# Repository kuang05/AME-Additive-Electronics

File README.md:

# AME · 增材电子一体化软件

> 从三维结构与 PCB 设计，到可打印的双材料 G-code —— 并把"这块板到底打不打得出来"量化成 0–100 分。

华为 ICT 大赛创新赛 · 赛题一（基于华为云产品打造 AI 创新应用）参赛作品。

---

## 这个软件解决什么问题

传统 PCB 打样依赖蚀刻、曝光、电镀，周期长、门槛高；普通 3D 打印机只能打塑料，不懂电气连接。

本软件把"电气设计"和"增材制造"接起来，回答一个两边都不回答的问题：

> **这块板，按这台机器、这套材料，到底打不打得出来？**

不做原理图编辑、不做三维建模、不做多机调度。只做"从已有设计到可打印路径"这一层，

并把可打性量化成规则与分数。

---

## 核心能力（四域 + 智能体）

| 域 | 能力 | 关键实现 |

|---|---|---|

| **结构** | STEP 导入（AP203/214/242，mm/inch，含装配体展平）、几何诊断、面分析、布尔建议预览、剖切测量 | 自研 B-Rep 平面/柱面/圆锥/球面/环面解析，18 类诊断码，3 份真实 CAD 文件实测 |

| **走线** | 板文件导入（KiCad/网表）、器件放置、手动布线、A* 自动布线、跳线、连通性检查 | 8 邻域栅格寻路 + 转弯惩罚 + 禁布区避让 |

| **可打性** | 七条工艺规则、0–100 评分、问题定位、中文原因与建议、热力图 | R1 线宽 / R2 间距 / R3 坡度 / R4 可达性 / R5 遮挡 / R6 温度场 / R7 介电流道 |

| **切片** | 三层双材料道次编排、坝-槽-坑几何、G-code 导出（确定性可复现） | 7 道次 / 总厚 0.44 mm；同一设计两次导出哈希一致 |

| **打印** | 虚拟打印、暂停/恢复、故障注入、缺陷归因、断电续打 | 缺陷归因到 设计/工艺/设备 三类 |

| **智能体** | 设计 Agent（检查→改→复检）、审查、裁决、计划重放 | 60 → 94 分；重放时设计摘要与 G-code 哈希双一致 |

**AI 有两条路径，定位不同**：

| 路径 | 定位 | 说明 |

|---|---|---|

| 华为云 **MaaS** 大模型（`ai/maas.py`） | **主线** | 赛题要求"调用大模型"。把规则违规翻译成可执行建议、做候选语义重排。OpenAI 兼容接口，默认 DeepSeek-V3-32K |

| 本地 26 维线性排序器（`ai/local.py`） | **离线降级** | 未配置密钥/断网时兜底。**这不是神经网络**——是解一次线性方程得到的系数，详见 [AI证据链.md](AI证据链.md) §0 |

降级链：MaaS → 本地线性 → 规则先验，任一层失败都不影响主流程。

---

## 两种交付形态，同一套算法内核

```

              ┌───────────────────────────────┐

              │  四域算法内核（约 6500 行）    │

              │  geometry / mrc / slicing /   │

              │  circuit / printing / ai      │

              │  纯函数，无数据库、无界面依赖  │

              └────────────┬──────────────────┘

                           │

                ┌──────────┴──────────┐

                │  ledger 命令总线     │

                │  （唯一写入口）      │

                └──────────┬──────────┘

                 ┌─────────┴─────────┐

           ┌─────┴─────┐       ┌─────┴──────┐

           │ 桌面版     │       │ 云上 Demo  │

           │ Tkinter   │       │ FastAPI    │

           │ AME.exe   │       │ 浏览器画布  │

           └─────┬─────┘       └─────┬──────┘

           ┌─────┴─────┐       ┌─────┴──────┐

           │  SQLite   │       │ RDS PG +   │

           │ 本地文件   │       │ Redis      │

           └───────────┘       └────────────┘

```

**有测试断言"同一设计在两端算出的分数完全相同"**——证明上云是换壳而非另写一套。

云上画布除了四域闭环，还做了六项查看/编辑交互（`tests/test_web_features.py` 24 项锁定）。

其中五项桌面版早有对应入口，**版本历史面板是这边第一次做成可浏览的界面**

（桌面版只在顶栏显示「版本 N」，PRJ-004 的数据一直在账本里、没有列表视图）：

| 交互 | 后端 | 说明 |

|---|---|---|

| 逐层播放 | `GET /api/projects/{pid}/layer/{index}` | 滑块 + 上/下一道次 + 起停点标记；路径取自库中那份切片，不重算 |

| 问题定位 | `GET /api/projects/{pid}/state` | 点问题列表自动高亮对应走线/焊盘 |

| 热力图 | `GET /api/projects/{pid}/heatmap` | 开关切换叠加，按对象累计扣分 |

| 规则阈值编辑 | `GET/POST /api/projects/{pid}/rules[/{code}]` | 七条规则逐个改阈值/启停；改阈值使规则版本 +1，保存即重评分（仅切启停不改版本） |

| 版本历史 | `GET /api/projects/{pid}/versions` | 每版序号、原因、分数前后与变更项 |

| 剖切 Z 阈值 | `GET /api/projects/{pid}/state` | 三维视图只画 Z ≤ 阈值的面，判据与桌面版一致 |

`state` 接口的 `faces` 带 `loop` / `normal` / `centroid` 顶点数据（超过 4000 个面时只下发前 4000 个，

并在 `faces_note` 说明被截断）。

---

## 快速开始

### 方式一：桌面版（离线，零依赖）

```bash

pip install shapely numpy pillow

python -m ame                    # 启动界面

python -m ame --selftest         # 11 步无界面自检

```

或用打包版：解压 `dist/AME/`，双击 `AME.exe`。

首次启动 → 工程 → 打开示例工程（一键看到完整链路）。

### 方式二：云上 Demo（浏览器）

```bash

pip install -r requirements-cloud.txt

python -m uvicorn ame.web.app:app --port 8000

# 打开 http://127.0.0.1:8000

```

或用 Docker：

```bash

docker compose up --build        # 含 PostgreSQL + Redis

```

### 方式三：接华为云 RDS + Redis

```bash

export AME_PG_DSN="postgresql://user:pass@<rds-host>:5432/ame"

export AME_REDIS_URL="redis://<redis-host>:6379/0"

python -m uvicorn ame.web.app:app --host 0.0.0.0 --port 8000

curl http://127.0.0.1:8000/api/health   # storage 应为 postgresql

```

详见 [云上部署与比赛材料.md](云上部署与比赛材料.md)。

---

## 复现验证（组委会按材料核对时用这个）

```bash

# 1. 全量测试（不含性能基准，约 8 分钟，离线）

python -m pytest -q -m "not perf"

# 2. 质量门禁（10 项客观指标）

python check_quality.py --full

# 3. 桌面版自检（11 步，无需显示环境）

python -m ame --selftest

# 4. 云端接口自检

python -m uvicorn ame.web.app:app --port 8000 &

curl -X POST http://127.0.0.1:8000/api/projects/sample

```

**预期结果**：886 项测试通过、2 项跳过（本机无 PostgreSQL，`psycopg` 未安装）；

门禁 9/10（`ame/geometry/stepio.py` 1384 行超出 1200 行阈值，其余 9 项通过）；

自检 11 步全过；示例工程 60 分 / 12 条问题；切片 7 道次 / 0.44 mm。

---

## 项目结构

```

ame/

├── ai/            收益排序（features / local / cloud / service / train）

├── agent/         设计·审查·裁决 Agent 与计划重放

├── circuit/       connectivity(判定) + routing(寻路) + kicad(导入)

├── db/            store(读写) + pg_store(PG) + storage(协议) + migrations + cache

├── geometry/      vec3 → types → syntax → assembly → stepio（严格单向依赖）

├── ledger/        errors + commands(写) + workspace(状态) + services

├── mrc/           engine（7 条规则，每条一个函数）

├── printing/      virtual（虚拟打印机与缺陷注入）

├── slicing/       raster(路径) + slicer(道次) + gcode(导出)

├── ui/            theme + app + _shell + _canvas + domains/*（7 个域）

└── web/           app(FastAPI) + static/index.html（浏览器画布）

```

读代码建议顺序：`ledger/commands.py` 的模块 docstring（写入口不变量）

→ `workspace.mrc_state()`（数据如何组装）→ 各域实现。

---

## 工程数据

| 指标 | 数值 |

|---|---|

| 代码规模 | `ame` 15,849 行 / 59 个模块 |

| 测试 | 710 项通过 + 2 项跳过（22 个测试文件） |

| 静态检查 | `ruff check ame/` 零违规 |

| 业务层类型注解 | 返回 76.6% / 参数 68.8% |

| 最大模块 | 1384 行（`geometry/stepio.py`；重构前为 3502 行的 `ui/app.py`） |

| 真实 CAD 验证 | 3 份（PRO/ENGINEER、Open CASCADE、SolidWorks，共约 800 KB） |

---

## 已知边界（主动说明）

| 边界 | 说明 |

|---|---|

| STEP 曲面 | 平面/柱面/圆锥（含圆台）/球面/环面可解析（面积用解析公式，三角网格只用于 `loop` 渲染，不参与面积）；B 样条/NURBS 等自由曲面仍不支持，标 `G-SURFACE-UNSUPPORTED`，面积取"包围盒与三角扇的较小值"保守低估。环面与球冠侧别不可判定时标 `G-SURFACE-APPROX` |

| 布尔运算 | 只做预览不执行（需求 V1 范围） |

| 真机联调 | 仅虚拟打印机，串口/网络协议已预留 |

| 多层过孔 | 首版不支持双层过孔与连续曲面切片 |

| 云上多用户 | 当前单用户演示；多租户需换 Redis 会话 + 每请求校验 |

| MindSpore/昇腾 | **未使用，也不宣称**。赛题一要求的是华为云产品（CodeArts/RDS/Redis），这三项均已接入 |

| PostgreSQL 实测 | 代码与方言转换已完成；本机（Python 3.13）无 psycopg wheel，真实 PG 集成需在有 RDS 时执行 |

---

## 文档索引

| 文档 | 内容 |

|---|---|

| [云上部署与比赛材料.md](云上部署与比赛材料.md) | 赛题一对应关系、部署步骤、CodeArts 留证、评委问答准备 |

| [赛题一改造方案.md](赛题一改造方案.md) | 云原生化技术裁决与施工记录 |

| [验收报告.md](验收报告.md) | 验收结论、测试分布、逐项实测记录 |

| [AI证据链.md](AI证据链.md) | 先说明「这里的 AI 是什么」、拟合数据、LOSO 交叉验证、降级链测试 |

| [重构记录.md](重构记录.md) | 架构拆分（模块边界、搬运方法、未做的取舍） |

| [质量提升记录.md](质量提升记录.md) | 缺陷清单、覆盖率、静态检查整改 |

| [用户操作说明.md](用户操作说明.md) | 五分钟演示路径、概念速查、快捷键 |

| [增材电子一体化软件_需求规格说明书.md](增材电子一体化软件_需求规格说明书.md) | 需求基线（唯一验收依据） |

---

## 许可

本项目采用 **Apache License 2.0**，详见 [LICENSE](LICENSE)。

允许商业使用、修改、分发，需保留版权声明与许可文本。

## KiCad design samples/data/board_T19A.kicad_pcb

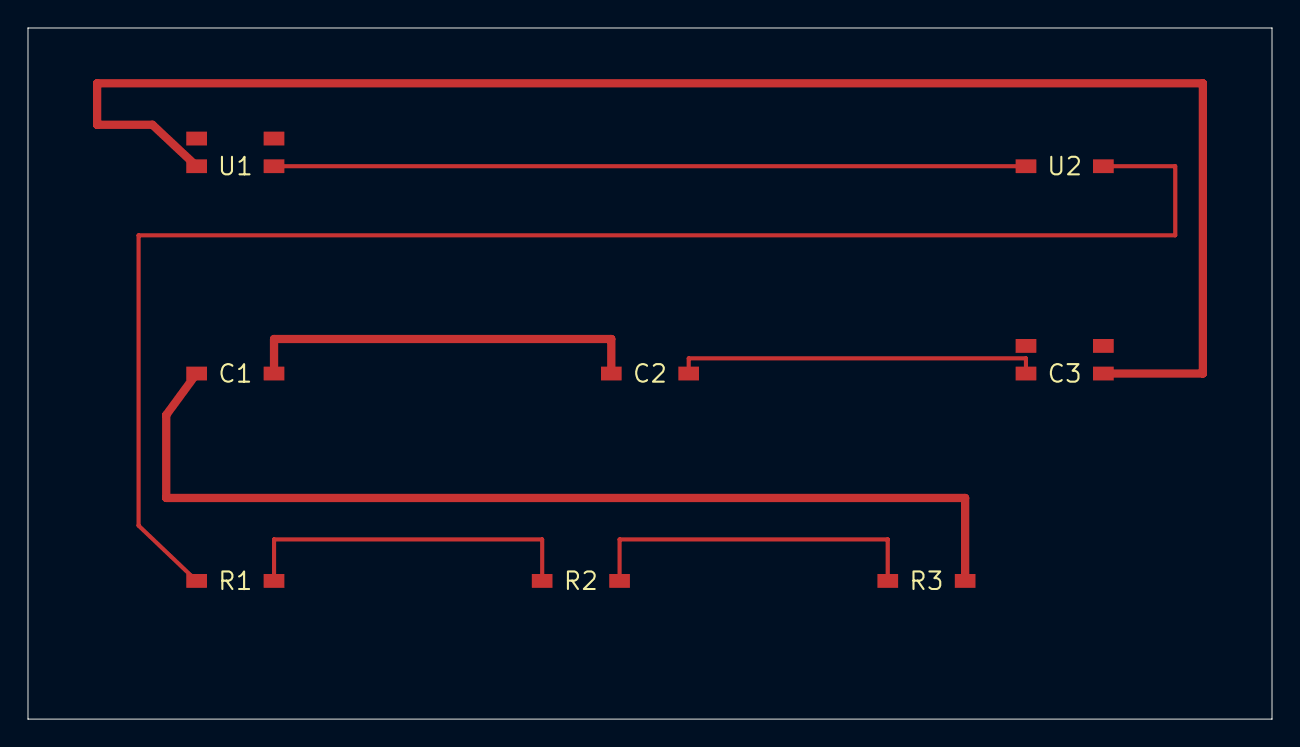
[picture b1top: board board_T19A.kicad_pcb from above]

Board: 0 copper layers, 90.0 x 50.0 mm, 8 parts (0 on the bottom side), 8 nets.

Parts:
C1, C2: R0603
C3: QFN8
R1, R2, R3: R0603
U1: QFN8
U2: R0603

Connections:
GND: C3.2, U1.1
N1: R1.1, U2.2
N2: R1.2, R2.1
N3: R2.2, R3.1
N4: C1.1, R3.2
N5: C1.2, C2.1
N6: C2.2, C3.1
VCC: U1.2, U2.1

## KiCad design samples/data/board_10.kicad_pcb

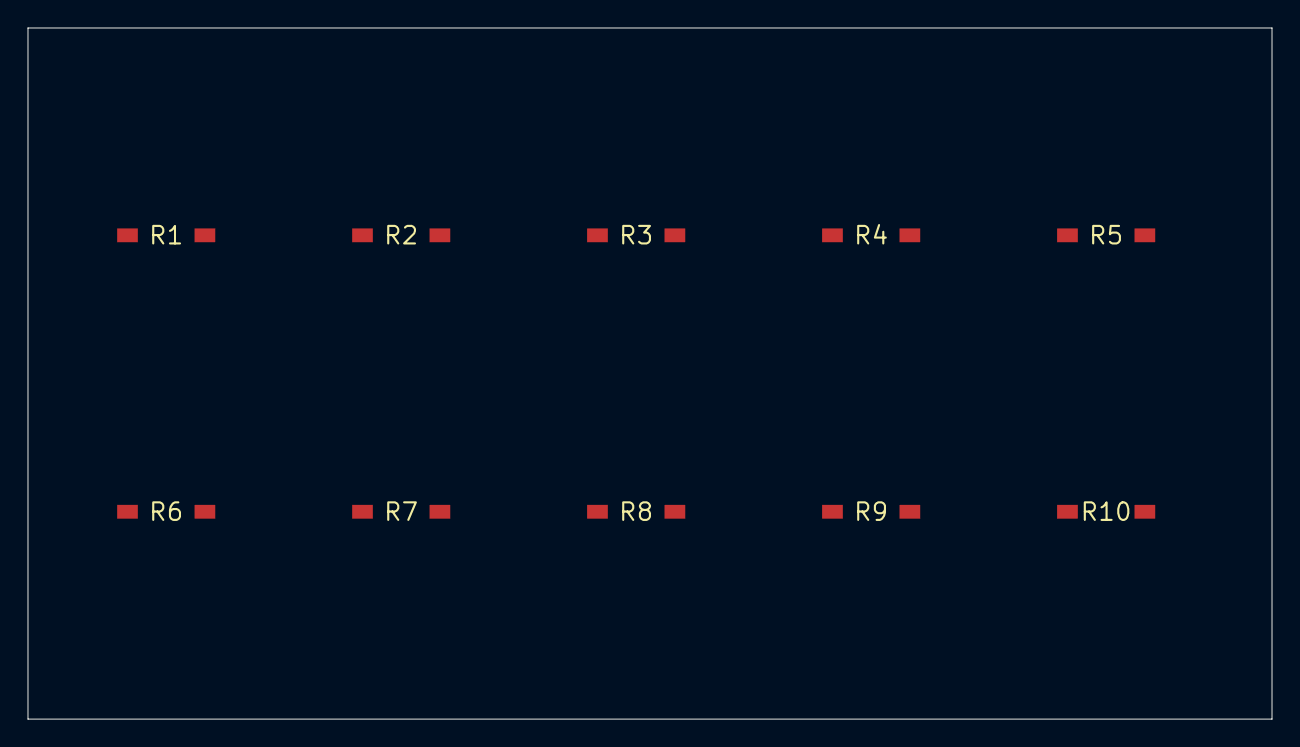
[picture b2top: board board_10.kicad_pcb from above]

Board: 0 copper layers, 90.0 x 50.0 mm, 10 parts (0 on the bottom side), 8 nets, no tracks yet.

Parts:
R1, R2, R3, R4, R5, R6, R7, R8, R9, R10: R0603

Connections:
N1: R1.1, R7.1
N2: R1.2, R7.2
N3: R2.1, R8.1
N4: R2.2, R8.2
N5: R3.1, R9.1
N6: R3.2, R9.2
N7: R4.1, R10.1
N8: R4.2, R10.2
